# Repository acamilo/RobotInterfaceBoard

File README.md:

### Robot Interface Board

The Robot Interface Board (RIB) is a breakout board for the [ESP32-DevKitC Arduino module](https://www.digikey.com/product-detail/en/espressif-systems/ESP32-DEVKITC-32D-F/1965-1003-ND/9693290). The Dev Kit C is a reference design of the ESP32-WROOM-32 module which houses the WiFi and bluetooth Antenae. The ESP32-WROOM-32 module houses an ESP32 microcontroller. 

#### Datasheet

[Arduino compatiple DevkitC]( https://esp-idf.readthedocs.io/en/latest/get-started/get-started-devkitc.html)

[ESP32 Microcontroller]( https://www.espressif.com/sites/default/files/documentation/esp32_datasheet_en.pdf)

[ESP32-DevKitC Arduino module wireing diagram ](https://dl.espressif.com/dl/schematics/esp32_devkitc_v4-sch-20180607a.pdf)

## PCB

## ESP32Dev Board PINMAP

## IO Pin counts

There are 16 I/O pins availible for use in your programs with no external perpheral already using them.

There are 21 I/O pins availible for use in your programs including the 5 output only strapping pins.

There are 27 I/O pins availible for use in your programs by reusing the boot button pin, serial pins and i2c pins for other purposes. 

## User Button

There is a button connected to pin 0 and is accessible to the users code as a button. If you hold it whild pressing the reset button, however, it will hold the chip in bootloader mode and it will not run your code until the core is reset or programmed over the USB. Once your code starts, this button is availible for use as a button in your code and pressing it will not effect the opperation of the core after your program has started.  

## Pins to Never Use because they will disrupt programming and opperation:

6-11    - These pins are hookups for external system flash and are used by the system flash. Unless you are extending the chips flash capibilities, do not use these. 

1 and 3 -  these are used to program the device and are serial port pins.

## Output Only Pins 

These pins are strapping pins for the core, if pulled to a different state than the default not boot.

These are strapping pins and have to be in known states at the time of the chip booting. If you use them as outputs, be careful to note the the pull up or down resistor states for each. When using these pins make sure the weak-pull resistor will not interfeare with your intended opperation, and do not add additional weak-pull resistors.

```
2  (pull down)
5  (pull up)
12 (pull down)
13 (pull up)
15 (pull up)
```
## Input Only pins

34-39 are input only. They have no output modes at all. Analog input and digital input are availible.

```
35
34
39
36
```

## Availible as Both Input and Output

```
4
14
16-19
21-23
25-27
32-33
```
## External Use pins

0 is the boot pin, if held low during a reset it will prevent the device from booting

1 and 3 are the serial port used for programming and print statements. This should not be used for user functions, but can be used if serial functionality is needed.

13 Has an LED connected to it on the RIB

22 and 21 have 4.7kOhm pullups on them and are connected to the Wii accessory port. These can be used with other i2c devices.
See: https://github.com/acamilo/RobotInterfaceBoard/issues/31

27 Is connected to the Wii header as controller detect. When the controller is connected, this is pulled to 3.3v. It is open when the controller is not connected.  

## Availible Servo/PWM/AnalogWrite Pins

The ESP32 can generate up to 16 simultanious Servo signels. 

```
4     
5    
12-19 
21-23 
25-27 
32-33 
```

### Timer distribution for PWM
The ESP32 has 4 timers availible for use in PWM generation. All PWM channels using a given timer have the same base frequency. Changing the frequency of a channel will change the frequency of other channels. Note the chart for how the PWM channel allocations coorospond to timers:

```
/*
 * LEDC Chan to Group/Channel/Timer Mapping
** ledc: 0  => Group: 0, Channel: 0, Timer: 0
** ledc: 1  => Group: 0, Channel: 1, Timer: 0
** ledc: 2  => Group: 0, Channel: 2, Timer: 1
** ledc: 3  => Group: 0, Channel: 3, Timer: 1
** ledc: 4  => Group: 0, Channel: 4, Timer: 2
** ledc: 5  => Group: 0, Channel: 5, Timer: 2
** ledc: 6  => Group: 0, Channel: 6, Timer: 3
** ledc: 7  => Group: 0, Channel: 7, Timer: 3
** ledc: 8  => Group: 1, Channel: 0, Timer: 0
** ledc: 9  => Group: 1, Channel: 1, Timer: 0
** ledc: 10 => Group: 1, Channel: 2, Timer: 1
** ledc: 11 => Group: 1, Channel: 3, Timer: 1
** ledc: 12 => Group: 1, Channel: 4, Timer: 2
** ledc: 13 => Group: 1, Channel: 5, Timer: 2
** ledc: 14 => Group: 1, Channel: 6, Timer: 3
** ledc: 15 => Group: 1, Channel: 7, Timer: 3
*/
```

When using ESP32PWM objects, changing the frequency will check for timer cross-talk. If you re-set the frequency of a PWM indirectly, the object will print this warning:

```
	WARNING PWM channel 1 shares a timer with 0
	changing the frequency to 330.00 Hz will ALSO change channel 0 
	from its previous frequency of 50.00 Hz
```

If you get this warning you can space out the attach events of the hardware using ESP32PWM using dummy objects. To consume a channel without activating a pwm, you can add this to your code between attach method calls. 

```
ESP32PWM dummy;
dummy.getChannel();
```
## Availible DAC pins
```
25
26
```
These pins when used with analogWrite will produce an 8 bit analog value on the given pin. The value is from 0-3.3v mapped to 0-255 values. The api is to simply use analogWrite().

## Interrupt

For code examples: https://techtutorialsx.com/2017/09/30/esp32-arduino-external-interrupts/

Availible interruptable pins are all input pins.

# Development Computer Options  

## Option 1) A lab machine

Availible to all students. 

Note that the driver is installed on these computers

Note that Arduino with the ESP32 toolchain is already installed in C:\WPIAPPS\arduino-1.8.3\

Note Eclipse is installed on all workstations with the Sloeber plugin installed. 

##  Option 2) Personal Machine

### Supported for this class

Windows 10 Pro 

A user name with no " " in the file path. Generally it is safe to use your WPI username as the username on your computer.

Fresh install is genearlly reccomended every 6 months. Install disk are availible to students as a resource from the WPI Helpdesk.

OneDrive and Dropbox conflict with the install process and must be fully removed from the user file paths. 

Eclipse should be installed in 

```
C:/eclipse
```

Arduino should be installed in 

```
C:/RBE-arduino-install/
```

After installation of both, ensure your user has write access to the directories. 

### Unsupported OS's

MacOS is unsupported and only intermittantly working. Drivers have been an issue with programming our board, and virtualization of Windows within OSX is tested non-working. If you have Mac OSX please install a fresh copy of Windows 10 nativly and dual boot. 

Ubuntu 16.04 is unsupported but works well.

Ubuntu 18.04 is unsupported but works well with some creative directions following. This will take more effort and would require pre-existing proficency in Linux. If you have 18.04 please install Windows 10 or 16.04. 

### How to get Windows 10 as a Student for free from WPI

To get your student copy of Windows go here: 

https://onlinestore.wpi.edu/

Select windows 10, and download it. For students you get one copy and it is free. 

You can follow this tutorial to install it:

https://www.youtube.com/watch?v=aTVOTY93XXU

# Arduino and the ESP32 Toolchain

This is installed on the lab machines already. 

After extracting the Zip file, install the 64 bit version of the driver. 

https://www.silabs.com/products/development-tools/software/usb-to-uart-bridge-vcp-drivers

Arduino IDE download :

https://github.com/WPIRoboticsEngineering/RobotInterfaceBoard/releases/download/rev5-1/RBE-arduino110718.zip

And extract it on your computer in 

```
C:/RBE-arduino-install/
```

Make a sketchbook folder in C:/, or (R:/ on the lab machines) make a folder:

```
C:/RBEArduino/
```

Make sure it is user level read-write

Run Arduino in the extracted folder.

Open the Preferences in Arduino and set the Sketchbook location to:

```
C:/RBEArduino/
```
Use [Arduino IDE and Github Desktop](https://github.com/WPIRoboticsEngineering/RobotInterfaceBoard/blob/master/UseArduinoGithubDesktop.md)

After your Arduino is installed and the ESP32 toolchain is up and running, open Arduino IDE and Select your board:

```
Tools->Board->ESP32 Dev Module
```

And select your port:

```
Tools->Port-> (the port that your arduino is connected to)
```

## Personal Computer install Linux / Mac  (Unsupported)

Ubuntu 18.04 Instructions:

[InstallToolchainOnUbuntu18-04.md](InstallToolchainOnUbuntu18-04.md)

Ubuntu 16.04 Instructions:

https://github.com/espressif/arduino-esp32/blob/master/docs/arduino-ide/debian_ubuntu.md

Mac instructions (NOT SUPPORTED BY RBE, HAS LOTS OF PROBLEMS):

https://github.com/espressif/arduino-esp32/blob/master/docs/arduino-ide/mac.md

## Install Eclipse And Setup Eclipse on Personal Machine

 [See Eclipse install instructions in InstallEclipse.md](https://github.com/WPIRoboticsEngineering/RobotInterfaceBoard/blob/master/InstallEclipse.md)
 
 [Open Projects in Eclipse using the Eclipse instructions](https://github.com/WPIRoboticsEngineering/RobotInterfaceBoard/blob/master/UseEclipse.md)

# Arduino Libraries
## HOWTO
For detailed instructions on how libraries work, see: https://www.arduino.cc/en/Guide/Libraries

Open Arduino and select Sketch->Libraries -> Manage Libraries
## Which Libraries

### 1001

ESP32Servo

ESP32Encoder

### 2001
Search for and install:

ESP32Servo

ESP32Encoder

Esp32SimplePacketComs

SimplePacketComs

### 2002
Search for and install:

ESP32Servo

ESP32Encoder

Adafruit_BNO055

Adafruit Unified Sensor

Esp32SimplePacketComs

SimplePacketComs

DFRobotIRPosition

# FAQ and troubleshooting

### "I dont see 'ESP32 Dev Module' as an option in Arduino when I try to select my board..."

* Use a lab machine. This will not be a problem on the lab machines. 

* You need to install the ESP 32 toolchain. See https://github.com/WPIRoboticsEngineering/RobotInterfaceBoard#personal-computer-install-windows--supported

### "I can compile the code but I do not have a serial port option in Arduino..."

* Ensure the driver installed https://github.com/WPIRoboticsEngineering/RobotInterfaceBoard#personal-computer-install-windows--supported

* If its a MAC, this is the issue that causes us to say MacOS is UNSUPPORTED. Install Windows https://github.com/WPIRoboticsEngineering/RobotInterfaceBoard#how-to-get-windows-10-as-a-student-for-free-from-wpi

* Make sure the USB Micro cable is a data cable, not just a crappy USB charging cable with no data lines. 

### "I can select the correct serial port, put it wont program or times out while programming..."

* Program an example script using Lab computer   (if this works have them re-download the pre-packaged arduino from https://github.com/WPIRoboticsEngineering/RobotInterfaceBoard#personal-computer-install-windows--supported ) 

* Is the serial moniter open? Close it and try again. 

* Did it program earlier? Unplug the USB and plug it back in.

* Hold Boot button and Strobe the enable button to set core into bootloader mode. Try to program. (If this helps, you are printing too much data to the serial port)

* Unplug everything from all IO (If this fixes it, check the pins and voltages, also check for diode dead-shorts check https://github.com/WPIRoboticsEngineering/RobotInterfaceBoard#pins-to-never-use )

* Check to see if the processor or regulator is HOT. If it is, a dead-short or over-voltage event occured and the device is dead forever. Replace. 

### "I can program it but it but it keeps rebooting over and over..."

* Null pointers are the #1 cause of this behavior, use print statements to isolate the point where it reboots and check for null pointers. This is the issue 9 out of 10 times. 

* Interrupt issues - Interrupts that access memory that is used by non-interrupt code without a mutex or semiphore. Try disabling the interrupt and if this fixed the reboot issue, then go ahead and implement the mutex locking. 

* Something may also be plugged into one of the off-limits pins, or your code is reconfiguring and messing up one of these pins. See: https://github.com/WPIRoboticsEngineering/RobotInterfaceBoard#pins-to-never-use 

### "This processor seems more complicated than the Uno and the Mega, why are we using it?"

* The ESP32 is a faster core at 260Mhz, vs the 16Mhz Uno. It is also dual-core.

* It has more perpherals needed for building robots, 16x 12 bit ADC, 2x DAC and 16 hardware encoder perpherals

* It has hardware and software that support WiFi for communications. 

* 32 bit processing with an FPU means complex math is possible on the microcontroller. 

* It is Arduino compatible for programming and Library support

* It is an open source design of the DevKit-C module, using an open source MIPS core and open soruce tool-chain

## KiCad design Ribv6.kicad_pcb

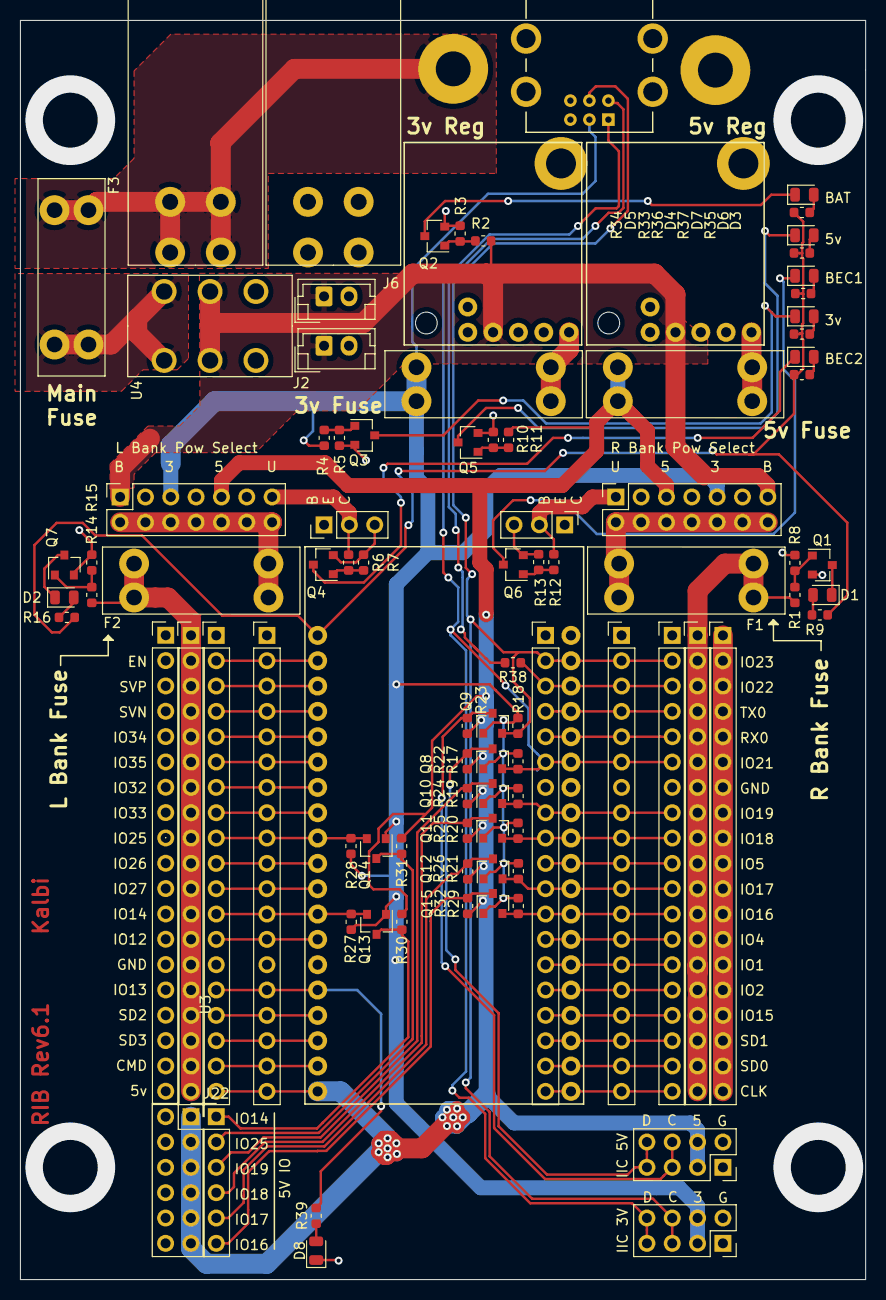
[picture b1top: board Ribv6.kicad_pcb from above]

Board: 4 copper layers, 84.7 x 126.2 mm, 95 parts (0 on the bottom side), 80 nets.

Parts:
D1, D2, D3, D4, D5, D6, D7, D8: LED_Small; LED_0805_2012Metric
F1, F2, F3, F4, F5: Fuse; 3557-2
J1, J9: Conn_01x03; PinHeader_1x03_P2.54mm_Vertical
J2, J6: Conn_01x02_Female; JST_EH_B2B-EH-A_1x02_P2.50mm_Vertical
J3, J5, J7, J10, J13, J16, J19, J20, J21: Conn_01x19; PinHeader_1x19_P2.54mm_Vertical
J4, J8: Conn_02x07_Odd_Even; PinSocket_2x07_P2.54mm_Vertical
J11, J26: Conn_01x01_Male; P315100rH
J12, J24: Conn_01x01_Male; MountingHole_3.5mm_Pad
J14, J15: Conn_02x04_Odd_Even; PinSocket_2x04_P2.54mm_Vertical
J22: Conn_01x06; PinHeader_1x06_P2.54mm_Vertical
J23: Conn_02x06_Odd_Even; PinSocket_2x06_P2.54mm_Vertical
J25: Conn_01x06; CONN_WII
Q1, Q2, Q3, Q4, Q5, Q6, Q7, Q8, Q9, Q10, Q11, Q12, Q13, Q14, Q15: BSS138; SOT-23
R1, R2, R3, R4, R5, R6, R7, R8, R10, R11, R12, R13, R14, R15, R34: R_Small; R_0603_1608Metric
R9, R16, R33, R35, R36, R37, R39: 330; R_0603_1608Metric
R17, R18, R19, R20, R21, R22, R23, R24, R25, R26, R27, R28, R29, R30, R31, R32, R38: 10k; R_0603_1608Metric
U1, U2: polulu-3784-D36V28F7
U3: esp-devkit; ESP-DEVKIT
U4: DPDT_x2; GF-126-0327

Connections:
+3.3VA: R9.2, R16.2, R33.2, R34.2, R35.2, R36.2, R37.2, U3.3V3
+3V3: F4.2, J4.9, J8.5, J14.3, J14.4, J25.3, Q8.1, Q9.1, Q10.1, Q11.1, Q12.1, Q13.1, Q14.1, Q15.1, R4.2, R17.2, R18.2, R19.2, R20.2, R21.2, R27.2, R28.2, R29.2
+5V: F5.2, J4.5, J8.9, J13.19, J15.3, J15.4, J16.19, J23.1, J23.3, J23.5, J23.7, J23.9, J23.11, R10.2, R22.2, R23.2, R24.2, R25.2, R26.2, R30.2, R31.2, R32.2, U3.5V
+BATT: J2.1, J4.13, J6.1, J8.1, R2.2, U1.VIN, U2.VIN, U4.2, U4.5
GND: D8.1, J1.3, J2.2, J3.1, J3.2, J3.3, J3.4, J3.5, J3.6, J3.7, J3.8, J3.9, J3.10, J3.11, J3.12, J3.13, J3.14, J3.15, J3.16, J3.17, J3.18, J3.19, J6.2, J9.3, J10.1, J10.2, J10.3, J10.4, J10.5, J10.6, J10.7, J10.8, J10.9, J10.10, J10.11, J10.12, J10.13, J10.14, J10.15, J10.16, J10.17, J10.18, J10.19, J13.14, J14.1, J14.2, J15.1, J15.2, J16.14, J19.7, J20.7, J21.7, J23.2, J23.4, J23.6, J23.8, J23.10, J23.12, J24.1, J25.6, J26.1, Q1.2, Q2.2, Q3.2, Q4.2, Q5.2, Q6.2, Q7.2, R3.1, R5.1, R7.1, R8.1, R11.1, R13.1, R15.1, U1.GND, U2.GND, U3.GND
GPIO14: J13.12, J16.12, Q13.2, R27.1, U3.IO14
GPIO14_5: J22.1, Q13.3, R30.1
GPIO16: J19.12, J20.12, J21.12, Q15.2, R29.1, U3.IO16
GPIO16_5: J22.6, Q15.3, R32.1
GPIO17: J19.11, J20.11, J21.11, Q12.2, R21.1, U3.IO17
GPIO17_5: J22.5, Q12.3, R26.1
GPIO18: J19.9, J20.9, J21.9, Q11.2, R20.1, U3.IO18
GPIO18_5: J22.4, Q11.3, R25.1
GPIO19: J19.8, J20.8, J21.8, Q10.2, R19.1, U3.IO19
GPIO19_5: J22.3, Q10.3, R24.1
GPIO25: J13.9, J16.9, Q14.2, R28.1, U3.IO25
GPIO25_5: J22.2, Q14.3, R31.1
unnamed: D1.1, Q1.3
unnamed: D1.2, R9.1
unnamed: D2.1, Q7.3
unnamed: D2.2, R16.1
unnamed: D3.1, Q2.3
unnamed: D3.2, R35.1
unnamed: D4.1, Q3.3
unnamed: D4.2, R33.1
unnamed: D5.1, Q4.3
unnamed: D5.2, R34.1
unnamed: D6.1, Q5.3
unnamed: D6.2, R37.1
unnamed: D7.1, Q6.3
unnamed: D7.2, R36.1
unnamed: D8.2, R39.1
unnamed: F1.1, J4.2, J4.4, J4.6, J4.8, J4.10, J4.12, J4.14
unnamed: F2.1, J8.2, J8.4, J8.6, J8.8, J8.10, J8.12, J8.14
unnamed: F3.1, J11.1, J12.1
unnamed: F3.2, U4.3, U4.4
unnamed: F4.1, U1.VOUT
unnamed: F5.1, U2.VOUT
unnamed: J13.2, J16.2, U3.EN
unnamed: J13.3, J16.3, U3.SVP
unnamed: J13.4, J16.4, U3.SVN
unnamed: J13.5, J16.5, U3.IO34
unnamed: J13.6, J16.6, U3.IO35
unnamed: J13.7, J16.7, U3.IO32
unnamed: J13.8, J16.8, U3.IO33
unnamed: J13.10, J16.10, U3.IO26
unnamed: J13.11, J16.11, U3.IO27
unnamed: J13.13, J16.13, U3.IO12
unnamed: J13.15, J16.15, R39.2, U3.IO13
unnamed: J13.16, J16.16, U3.SD2
unnamed: J13.17, J16.17, U3.SD3
unnamed: J13.18, J16.18, U3.CMD
unnamed: J19.3, J20.3, J21.3, R38.1, U3.IO22
unnamed: J19.4, J20.4, J21.4, U3.TX0
unnamed: J19.5, J20.5, J21.5, U3.RX0
unnamed: J19.10, J20.10, J21.10, U3.IO5
unnamed: J19.13, J20.13, J21.13, U3.IO4
unnamed: J19.14, J20.14, J21.14, U3.IO1
unnamed: J19.15, J20.15, J21.15, U3.IO2
unnamed: J19.16, J20.16, J21.16, U3.IO15
unnamed: J19.17, J20.17, J21.17, U3.SD1
unnamed: J19.18, J20.18, J21.18, U3.SD0
unnamed: J19.19, J20.19, J21.19, U3.CLK
unnamed: Q1.1, R1.1, R8.2
unnamed: Q2.1, R2.1, R3.2
unnamed: Q3.1, R4.1, R5.2
unnamed: Q4.1, R6.1, R7.2
unnamed: Q5.1, R10.1, R11.2
unnamed: Q6.1, R12.1, R13.2
unnamed: Q7.1, R14.1, R15.2
unnamed: U4.1, U4.6
Rail1: F1.2, J5.1, J5.2, J5.3, J5.4, J5.5, J5.6, J5.7, J5.8, J5.9, J5.10, J5.11, J5.12, J5.13, J5.14, J5.15, J5.16, J5.17, J5.18, J5.19, R1.2
Rail2: F2.2, J7.1, J7.2, J7.3, J7.4, J7.5, J7.6, J7.7, J7.8, J7.9, J7.10, J7.11, J7.12, J7.13, J7.14, J7.15, J7.16, J7.17, J7.18, J7.19, R14.2
SCL_5: J15.5, J15.6, Q9.3, R23.1
SCL_33: J14.5, J14.6, J19.2, J20.2, J21.2, J25.4, Q9.2, R18.1, U3.IO23
SDA_5: J15.7, J15.8, Q8.3, R22.1
SDA_33: J14.7, J14.8, J19.6, J20.6, J21.6, J25.1, Q8.2, R17.1, U3.IO21
UBEC1: J1.2, J4.1, R12.2
UBEC2: J8.13, J9.2, R6.2
prez: J25.2, R38.2

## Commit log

2017-11-30 Rev 3 commit
2018-02-15 Updated Locking connecter library footprint with more clearence for locking pins
2018-02-15 Updated PCB footprints with updated wiichuck footprint
2018-02-15 Replaced JST power connectors with screw terminals
2018-02-15 Moved teensy power connector and added solder lugs for a cable to both boards
2018-02-15 ESP32 SDA now on pin 21
2018-02-27 label wii connector pins
2018-02-27 label Power and GND on battery connection
2018-02-27 DET pins routed to esp and teensy
2018-02-27 upped rev no to 4
2018-03-02 BOM and Centroid added
2018-03-02 Gerbers added
2018-03-02 DK parts for all lines
2018-03-22 Replaced fuseholder with blade style automotive fuse
2018-03-22 Added Power, Fuse, Regulated satus LEDs
2018-04-04 #28 Adding a readme
2018-04-04 Adding image
2018-04-12 Issue #35: Split esp32 board off into its own file
2018-04-12 Issue #26 Disconnect specific IO used by System Resources on ESP32
2018-04-12 Issue #32 ESP32 needs a user accessible LED on 13
2018-04-12 Issue #22 Solder lugs resized to 3MM diameter holes and moved
2018-04-12 Issue #19 4k7 ohm pullups to 3.3v are needed on SDA and SCL
2018-04-13 Issue #18 Fix footprint for fuse holder
2018-04-13 Issue #21 Added a pad for a PTC resetabble fuse for the 3.3v rail
2018-04-13 Issues #33 and 4 and #36
2018-04-13 Issue #34
2018-04-20 Resolved issue 37
2018-04-20 Resolved issue 38
2018-04-20 Resolved issue 31
2018-04-26 Resolved issue #24
2018-04-26 Resolved issue #23
2018-04-30 Resolved issue #27
2018-04-30 added board image and readme. #28
2018-04-30 Moving images into folder
2018-05-03 Moved fuse holder as per #40
2018-05-03 Updated silkscreen indicating analog pins #41
2018-05-03 updated board render to reflect new fuse location
2018-05-07 Updated BOM. #20 #25
2018-05-07 Removed binaries
2018-06-06 added missing fuse and diode to BOM
2018-07-16 changed 5v rail
2018-07-16 Removed Extra folder
2018-07-16 Fixed R1-4 in bom
2018-08-02 Updated centroid to include surface mount and through hole compnents
2018-08-02 added JP9 to BOM
2018-09-24 docs initial commit
2019-01-11 adding setup docs to board readme
2019-01-11 moved teh doc to docs
2019-02-01 Add 18.04 instructions
2019-02-01 Fix instructions link
2019-03-27 highlight the button to press
2019-03-27 Create setESPConfigs.png
    Adding espconfig
2019-06-19 Added polulu DC-DC
2019-06-19 added devkit PCB
2019-06-19 Added headers
2019-06-19 power jumpers for rails.
2019-06-19 Add rail fuse and fuse indicators
2019-06-24 add temp files to gitignore
2019-06-24 i2c circuit
2019-06-24 Update Ribv6.sch
    Added level hifting for 19,18,17,16,25,14
2019-06-24 Added indicator LEDS
2019-06-24 Battery Connector
2019-06-24 Extra header to accomidate shorter modules
2019-06-25 Update Ribv6.sch
    Added connectors for 5v
    removed extra header.
2019-07-02 Fuse FP
2019-07-02 Wii conn FP
2019-07-02 bananna FP
2019-07-02 added new features to sch
2019-07-02 first iter of PCB
2019-07-02 Removed eagle BRD
2019-07-02 fewer i2c conns in schematic
2019-07-08 routing draft
2019-07-08 layout done, partial silk
2019-10-16 Added lib for switch.
2019-10-16 re-laying out power section.
2019-10-18 Update polulu-3784-D36V28F7.kicad_mod
    Changed top rigt hole to recieve solderable standoff.
2019-10-21 more routing
2019-10-22 finished routing.
2019-10-22 Added LED on pin 13
    #6
2020-01-17 Board Updates.
    #3 Updated power system for the rib
    * Bolt holes on a 5.5mm grid
    * Second ehader added so narrow ESP32 devkit can be used
    * Accepts a 7.5 to 18v battery with solder lugs and bannana plugs
    * 5v 2 amp REG for esp32
    * 2 external power converter ports
2020-01-17 Added labels to power lugs, Bannana jacks #12
    Added labels to power lugs, Bannana jacks #12
